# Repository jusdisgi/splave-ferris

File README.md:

# splave-ferris
Simple 34-key split ergonomic keyboard running ZMK on a Seeed XIAO BLE controller and (eventually) supporting multiple switch types. Similar in layout to the Ferris Sweep except with a bit of finger splay.

My goals are to make the keyboard as small and thin as possibe while remaining comfortable, efficient, and relatively durable. That is the main rationale for not using hotswap switches; in addition to adding a bit of height, it makes the keys much less secure if you aren't using a case of some kind. I intend to plastidip the bottom and otherwise leave it raw.

The board is designed to be primarily assembled with SMD methods. I intend to use solder paste and a hotplate to surface mount the controller, button, switch, and all the diodes, leaving only the battery connector and keyswitches to manually solder. I may even experiment with doing those with a hot air rework station. In any case this is why the back is totatlly devoid of components.

At the moment I have only done the Choc v1 version, but I expect to have more soon. The layout is done in ergogen, so it's relatively easy to adapt as needed. The next switch implemented will likely be the new Kailh CPG1316S ultra-low profile scissor switch. In addition to being extremely low-profile, it is a surface-mount part; with an appropriate battery connector, I may be able to design it so it required no manual soldering at all.

I created a schematic, but while I believe it to be accurate, it is not connected to the PCB files in any way, as they were generated by ergogen.

I remain very new at all this stuff. So if you see something wrong, please let me know!

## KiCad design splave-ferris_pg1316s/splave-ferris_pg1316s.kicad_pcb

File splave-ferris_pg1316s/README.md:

# splave-ferris_pg1316s
A version of splave-ferris using the new Kailh PG1316S Ultra-low-profile scissor switches.

For more on the splave-ferris generally, see the readme in the base directory.

There are quite a few changes from the choc version of the board. Here are the most notable I could think of:

1. Keycaps for these switches are 16x16mm, so I changed the spacing accordingly. Several other dimensions were changed as needed.
2. I changed the battery connector from a JST to a Molex Pico EZMate, which surface mounts and has a much lower profile.
3. I removed the reset button, as the XIAO has one built in and this is my most minimalist design.
4. Battery connector and power switch are in new positions.
5. I switched from SOD-123 diodes to SOD-323 due to the diode pocket on the PG1316 having only 1.2mm of headspace.
6. Everything on the board is surface mount, and nothing is on the back of the board. This one can be manufactured in a single hotplate run.
7. The routing is somewhat cleaner, despite the all-SMD design requiring a lot of vias. I think I'm getting better.

As with the choc version, this is intended to be used without a case.

I created a schematic, but while I believe it to be accurate, it is not connected to the PCB files in any way, as they were generated by ergogen. Also, the PCB files you likely want are the _left and _right versions...the one without a direction includes both halves of the board, but the nets are all the same to that may cause problems. It is also unrouted, although if you do wish to do the routing differently there are also unrouted versions of each half.

I have included production gerber files. I am planning on ordering them soon, but as yet they are untested.

I remain very new at all this stuff. So if you see something wrong, please let me know!

Here are some pics...

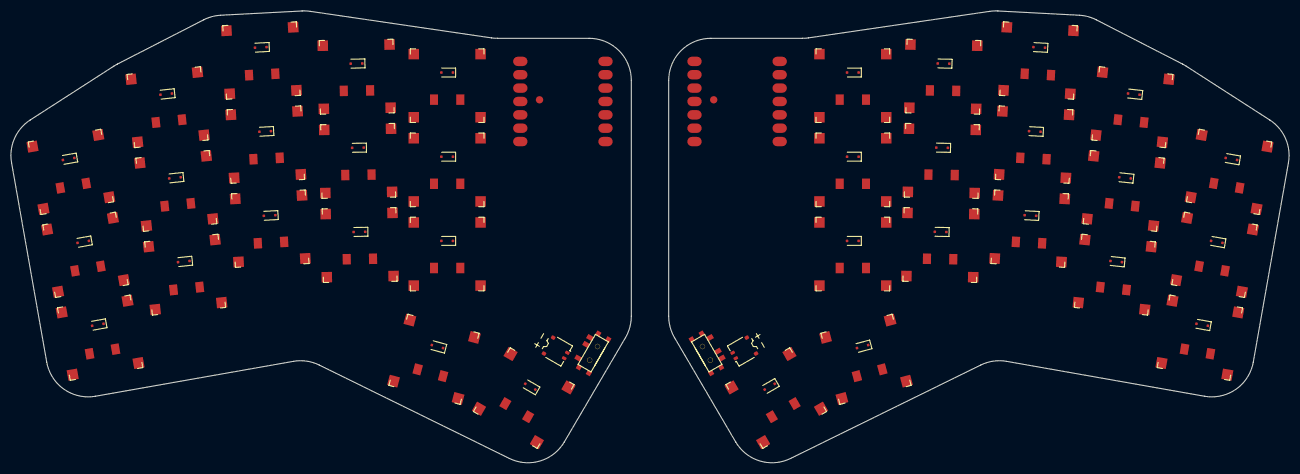
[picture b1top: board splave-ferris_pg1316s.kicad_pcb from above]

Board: 2 copper layers, 242.9 x 85.9 mm, 74 parts (0 on the bottom side), 55 nets, no tracks yet.

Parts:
CONN1, CONN2: battery_connector_molex_pico_ezmate_1x02
D1, D2, D3, D4, D5, D6, D7, D8, D9, D10, D11, D12, D13, D14, D15, D16, D17, D18, D19, D20, D21, D22, D23, D24, D25, D26, D27, D28, D29, D30, D31, D32, D33, D34: D_SOD-323F
MCU1, MCU2: xiao_smd
S1, S2, S3, S4, S5, S6, S7, S8, S9, S10, S11, S12, S13, S14, S15, S16, S17, S18, S19, S20, S21, S22, S23, S24, S25, S26, S27, S28, S29, S30, S31, S32, S33, S34: PG1316S
T1, T2: SPDT_C128955

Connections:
BAT: MCU1.19, MCU2.19, T1.2, T2.1
BAT_P: CONN1.2, CONN2.2, T1.1, T2.2
CLK: MCU1.15, MCU2.15
D0: D3.2, D6.2, D9.2, D12.2, D15.2, D33.2, D34.2, MCU1.1, MCU2.1
D1: MCU1.2, MCU2.2, S7.2, S8.2, S9.2, S30.2, S31.2, S32.2, S34.2
D2: D2.2, D5.2, D8.2, D11.2, D14.2, MCU1.3, MCU2.3, S27.2, S28.2, S29.2, S33.2
D3: MCU1.4, MCU2.4, S4.2, S5.2, S6.2, S18.2, S19.2, S20.2
D4: D1.2, D4.2, D7.2, D10.2, D13.2, D18.2, D21.2, D24.2, D27.2, D30.2, MCU1.5, MCU2.5
D5: MCU1.6, MCU2.6, S1.2, S2.2, S3.2, S21.2, S22.2, S23.2
D6: MCU1.7, MCU2.7
D7: MCU1.8, MCU2.8
D8: D19.2, D22.2, D25.2, D28.2, D31.2, MCU1.9, MCU2.9, S10.2, S11.2, S12.2, S16.2
D9: D16.2, D17.2, MCU1.10, MCU2.10, S24.2, S25.2, S26.2
D10: D20.2, D23.2, D26.2, D29.2, D32.2, MCU1.11, MCU2.11, S13.2, S14.2, S15.2, S17.2
DIO: MCU1.16, MCU2.16
GND: CONN1.1, CONN2.1, MCU1.13, MCU1.18, MCU1.20, MCU2.13, MCU2.18, MCU2.20
NFC1: MCU1.21, MCU2.21
NFC2: MCU1.22, MCU2.22
RAW3V3: MCU1.12, MCU2.12
RAW5V: MCU1.14, MCU2.14
RST: MCU1.17, MCU2.17
far_fan: D17.1, S17.1
index_bottom: D10.1, S10.1
index_home: D11.1, S11.1
index_top: D12.1, S12.1
inner_bottom: D13.1, S13.1
inner_home: D14.1, S14.1
inner_top: D15.1, S15.1
middle_bottom: D7.1, S7.1
middle_home: D8.1, S8.1
middle_top: D9.1, S9.1
mirror_far_fan: D34.1, S34.1
mirror_index_bottom: D27.1, S27.1
mirror_index_home: D28.1, S28.1
mirror_index_top: D29.1, S29.1
mirror_inner_bottom: D30.1, S30.1
mirror_inner_home: D31.1, S31.1
mirror_inner_top: D32.1, S32.1
mirror_middle_bottom: D24.1, S24.1
mirror_middle_home: D25.1, S25.1
mirror_middle_top: D26.1, S26.1
mirror_near_fan: D33.1, S33.1
mirror_pinky_bottom: D18.1, S18.1
mirror_pinky_home: D19.1, S19.1
mirror_pinky_top: D20.1, S20.1
mirror_ring_bottom: D21.1, S21.1
mirror_ring_home: D22.1, S22.1
mirror_ring_top: D23.1, S23.1
near_fan: D16.1, S16.1
pinky_bottom: D1.1, S1.1
pinky_home: D2.1, S2.1
pinky_top: D3.1, S3.1
ring_bottom: D4.1, S4.1
ring_home: D5.1, S5.1
ring_top: D6.1, S6.1

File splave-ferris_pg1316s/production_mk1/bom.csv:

Designator,Footprint,Quantity,Value,LCSC Part #
CONN1,battery_connector_molex_pico_ezmate_1x02,1,,
"D1, D10, D11, D12, D13, D14, D15, D16, D17, D2, D3, D4, D5, D6, D7, D8, D9",D_SOD-323F,17,,
MCU1,xiao_smd,1,,
"S1, S10, S11, S12, S13, S14, S15, S16, S17, S2, S3, S4, S5, S6, S7, S8, S9",PG1316S,17,,
T1,SPDT_C128955,1,,

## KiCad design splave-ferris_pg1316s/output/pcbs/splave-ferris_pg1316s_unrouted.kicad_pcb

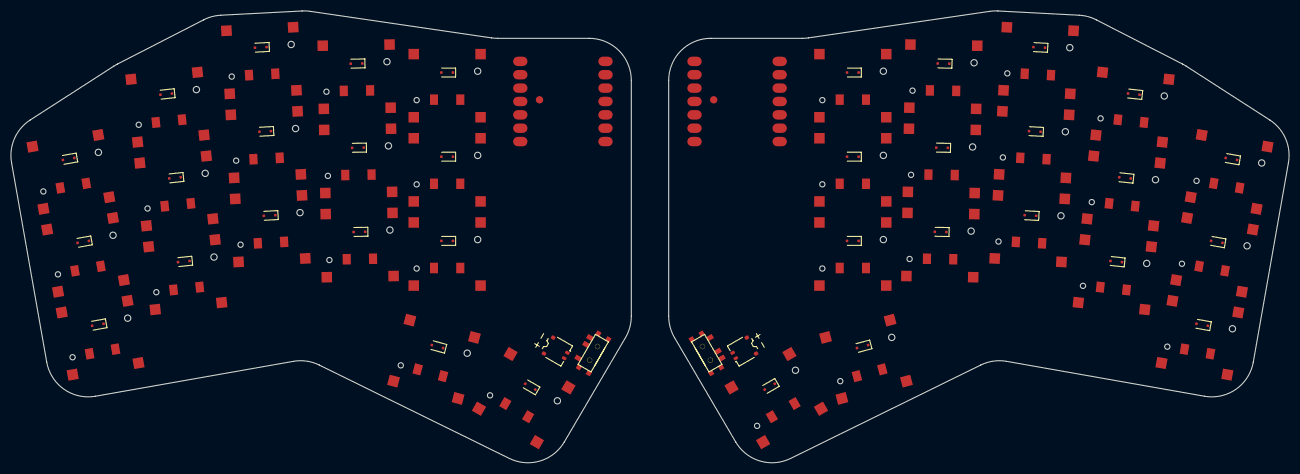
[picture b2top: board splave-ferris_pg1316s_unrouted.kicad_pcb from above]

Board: 2 copper layers, 242.9 x 85.9 mm, 74 parts (0 on the bottom side), 55 nets, no tracks yet.

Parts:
CONN1, CONN2: battery_connector_molex_pico_ezmate_1x02
D1, D2, D3, D4, D5, D6, D7, D8, D9, D10, D11, D12, D13, D14, D15, D16, D17, D18, D19, D20, D21, D22, D23, D24, D25, D26, D27, D28, D29, D30, D31, D32, D33, D34: D_SOD-323F
MCU1, MCU2: xiao_smd
S1, S2, S3, S4, S5, S6, S7, S8, S9, S10, S11, S12, S13, S14, S15, S16, S17, S18, S19, S20, S21, S22, S23, S24, S25, S26, S27, S28, S29, S30, S31, S32, S33, S34: CPG1316S01D02_mikeholscher
T1, T2: SPDT_C128955

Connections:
BAT: MCU1.19, MCU2.19, T1.2, T2.1
BAT_P: CONN1.2, CONN2.2, T1.1, T2.2
CLK: MCU1.15, MCU2.15
D0: D3.1, D6.1, D9.1, D12.1, D15.1, D33.1, D34.1, MCU1.1, MCU2.1
D1: MCU1.2, MCU2.2, S7.2, S8.2, S9.2, S30.2, S31.2, S32.2, S34.2
D2: D2.1, D5.1, D8.1, D11.1, D14.1, MCU1.3, MCU2.3, S27.2, S28.2, S29.2, S33.2
D3: MCU1.4, MCU2.4, S4.2, S5.2, S6.2, S18.2, S19.2, S20.2
D4: D1.1, D4.1, D7.1, D10.1, D13.1, D18.1, D21.1, D24.1, D27.1, D30.1, MCU1.5, MCU2.5
D5: MCU1.6, MCU2.6, S1.2, S2.2, S3.2, S21.2, S22.2, S23.2
D6: MCU1.7, MCU2.7
D7: MCU1.8, MCU2.8
D8: D19.1, D22.1, D25.1, D28.1, D31.1, MCU1.9, MCU2.9, S10.2, S11.2, S12.2, S16.2
D9: D16.1, D17.1, MCU1.10, MCU2.10, S24.2, S25.2, S26.2
D10: D20.1, D23.1, D26.1, D29.1, D32.1, MCU1.11, MCU2.11, S13.2, S14.2, S15.2, S17.2
DIO: MCU1.16, MCU2.16
GND: CONN1.1, CONN2.1, MCU1.13, MCU1.18, MCU1.20, MCU2.13, MCU2.18, MCU2.20
NFC1: MCU1.21, MCU2.21
NFC2: MCU1.22, MCU2.22
RAW3V3: MCU1.12, MCU2.12
RAW5V: MCU1.14, MCU2.14
RST: MCU1.17, MCU2.17
far_fan: D17.2, S17.1
index_bottom: D10.2, S10.1
index_home: D11.2, S11.1
index_top: D12.2, S12.1
inner_bottom: D13.2, S13.1
inner_home: D14.2, S14.1
inner_top: D15.2, S15.1
middle_bottom: D7.2, S7.1
middle_home: D8.2, S8.1
middle_top: D9.2, S9.1
mirror_far_fan: D34.2, S34.1
mirror_index_bottom: D27.2, S27.1
mirror_index_home: D28.2, S28.1
mirror_index_top: D29.2, S29.1
mirror_inner_bottom: D30.2, S30.1
mirror_inner_home: D31.2, S31.1
mirror_inner_top: D32.2, S32.1
mirror_middle_bottom: D24.2, S24.1
mirror_middle_home: D25.2, S25.1
mirror_middle_top: D26.2, S26.1
mirror_near_fan: D33.2, S33.1
mirror_pinky_bottom: D18.2, S18.1
mirror_pinky_home: D19.2, S19.1
mirror_pinky_top: D20.2, S20.1
mirror_ring_bottom: D21.2, S21.1
mirror_ring_home: D22.2, S22.1
mirror_ring_top: D23.2, S23.1
near_fan: D16.2, S16.1
pinky_bottom: D1.2, S1.1
pinky_home: D2.2, S2.1
pinky_top: D3.2, S3.1
ring_bottom: D4.2, S4.1
ring_home: D5.2, S5.1
ring_top: D6.2, S6.1

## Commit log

2025-04-14 Initial upload of Ergogen and KiCad assets. Complete choc v1, very early PG1316S work.
2025-04-15 Finalized choc_v1 design and created production files.
2025-04-16 Add PG1316S version including schematics, PCB files, and ergogen config/footprints.
2025-04-16 Delete splave-ferris_cpg1316s directory
    This was replaced by the pg1316s directory once I figured out how to get that switch working as an ergogen footprint.
2025-04-16 Delete PG1316S directory
    Superceded by splave-ferris_pg1316s directory
2025-04-17 Complete routing for PG1316S variant, create production files.
2025-04-18 Add multidiode package footprints.
2025-04-30 Add stablizer holes to PG1316S footprint, regenerate PCB files.
2025-04-30 Add comments to new footprint file.
